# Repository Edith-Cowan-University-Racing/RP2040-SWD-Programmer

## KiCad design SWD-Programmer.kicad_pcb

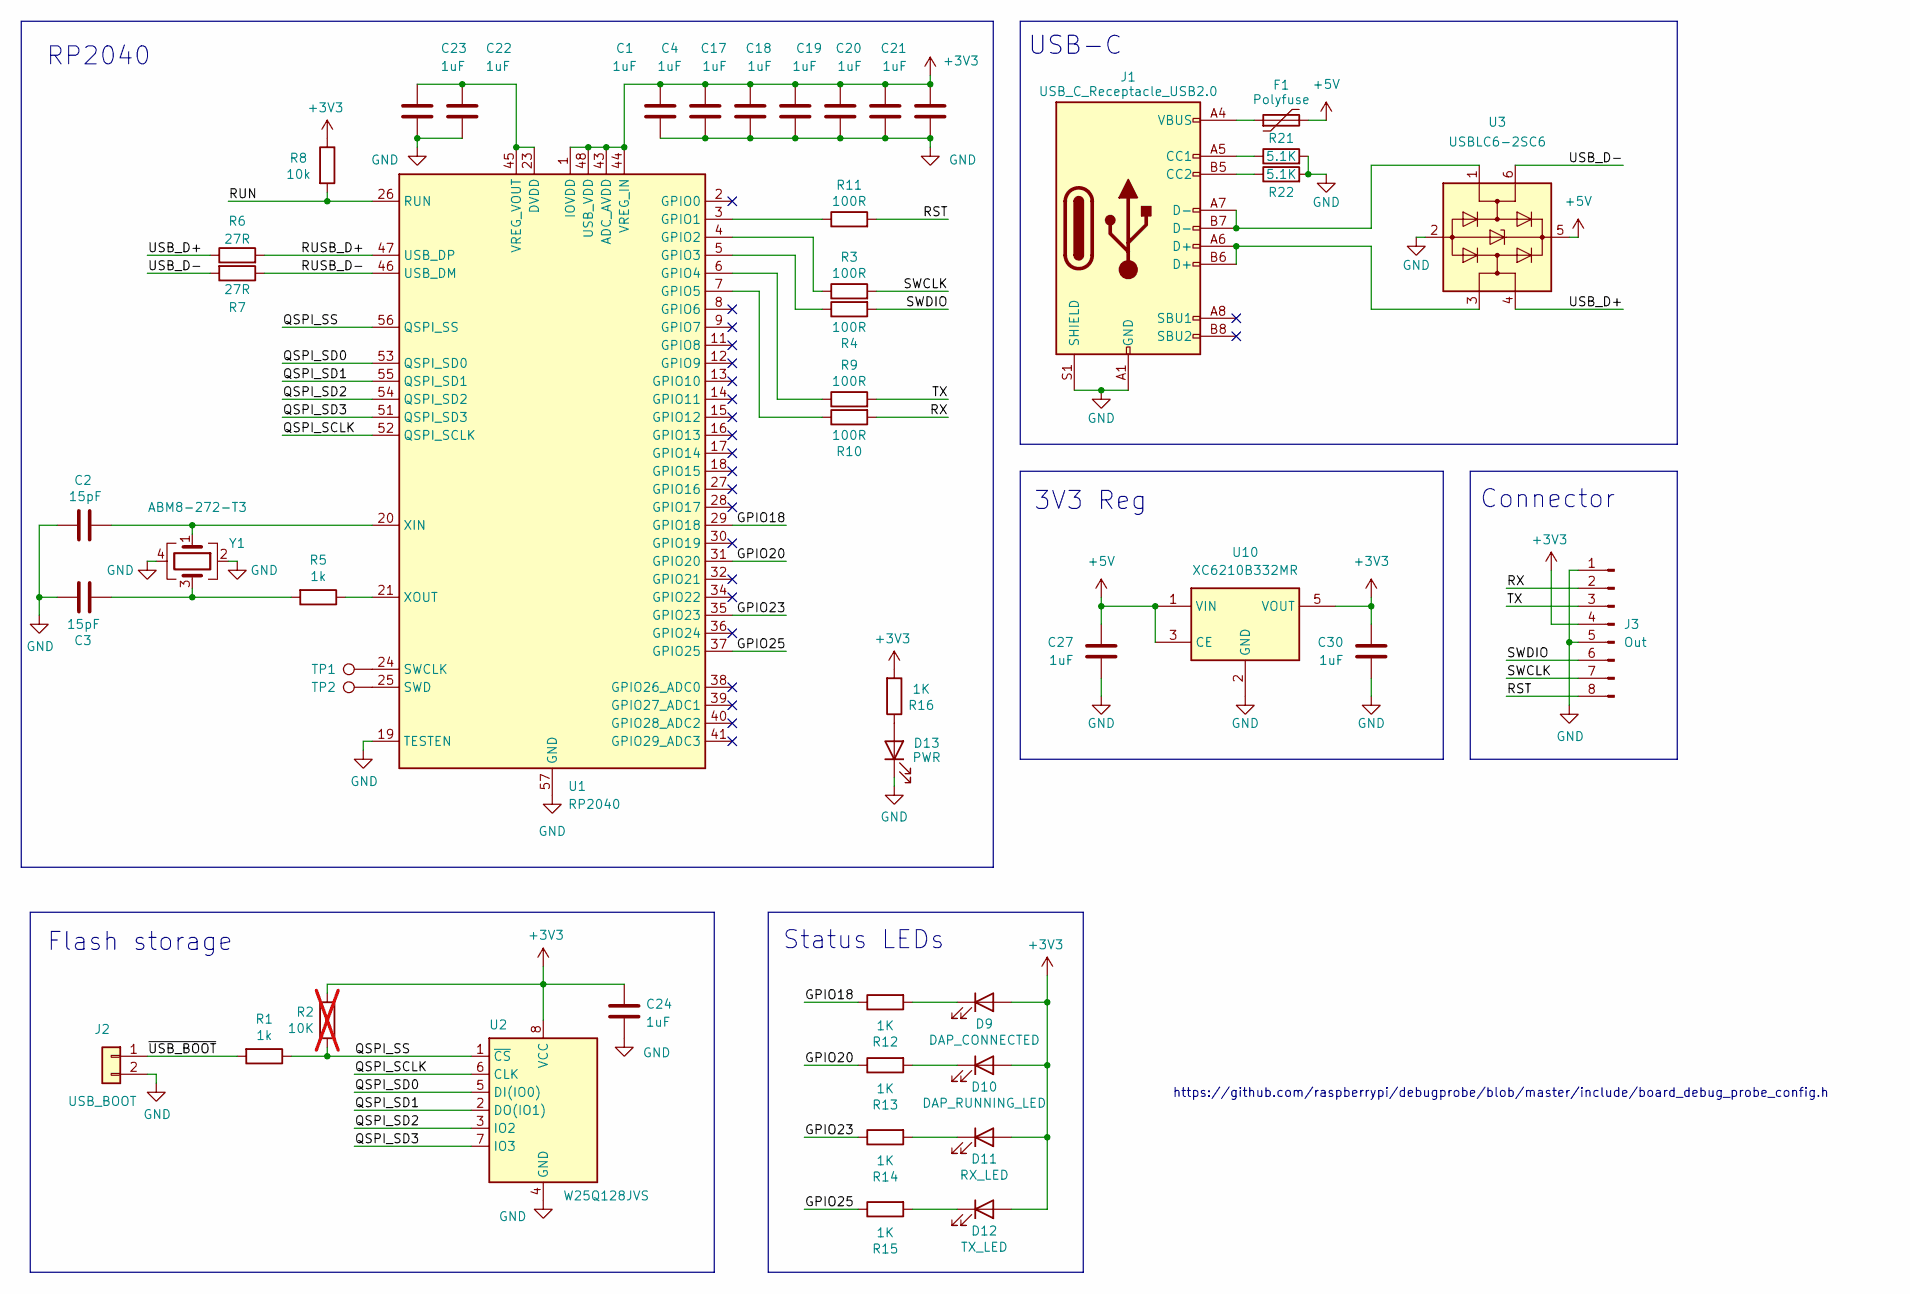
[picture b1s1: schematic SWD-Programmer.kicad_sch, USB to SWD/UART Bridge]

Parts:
C1, C4, C17, C18, C19, C20, C21, C22, C23, C24, C27, C30: 1uF; C_0603_1608Metric
C2, C3: 15pF; C_0603_1608Metric
D9: DAP_CONNECTED; LED_0805_2012Metric
D10: DAP_RUNNING_LED; LED_0805_2012Metric
D11: RX_LED; LED_0805_2012Metric
D12: TX_LED; LED_0805_2012Metric
D13: PWR; LED_0805_2012Metric
F1: Polyfuse; Fuse_0805_2012Metric
J1: USB_C_Receptacle_USB2.0; U263-163N-4OS1735
J2: USB_BOOT; PinHeader_1x02_P1.27mm_Vertical
J3: Out; PinHeader_1x08_P2.54mm_Horizontal
R1, R5: 1k; R_0603_1608Metric
R2: 10K; R_0603_1608Metric; not fitted
R3, R4, R9, R10, R11: 100R; R_0603_1608Metric
R6, R7: 27R; R_0603_1608Metric
R8: 10k; R_0603_1608Metric
R12, R13, R14, R15, R16: 1K; R_0603_1608Metric
R21, R22: 5.1K; R_0603_1608Metric
TP1, TP2: TestPoint; TestPoint_Pad_D2.0mm
U1: RP2040; QFN-56-1EP_7x7mm_P0.4mm_EP3.2x3.2mm
U2: W25Q128JVS; SOIC-8_5.3x5.3mm_P1.27mm
U3: USBLC6-2SC6; SOT-23-6; LCSC C2827654
U10: XC6210B332MR; SOT-23-5
Y1: ABM8-272-T3; Crystal_SMD_3225-4Pin_3.2x2.5mm

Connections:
+3V3: C1.1, C4.1, C17.1, C18.1, C19.1, C20.1, C21.1, C24.1, C30.1, D9.2 (A), D10.2 (A), D11.2 (A), D12.2 (A), J3.4, R2.1, R8.1, R16.2, U1.1 (IOVDD), U1.10 (IOVDD), U1.22 (IOVDD), U1.33 (IOVDD), U1.42 (IOVDD), U1.43 (ADC_AVDD), U1.44 (VREG_IN), U1.48 (USB_VDD), U1.49 (IOVDD), U2.8 (VCC), U10.5 (VOUT)
+5V: C27.1, F1.2, U3.5 (VBUS), U10.1 (VIN), U10.3 (CE)
/GPIO18: R12.1, U1.29 (GPIO18)
/GPIO20: R13.1, U1.31 (GPIO20)
/GPIO23: R14.1, U1.35 (GPIO23)
/GPIO25: R15.1, U1.37 (GPIO25)
/QSPI_SCLK: U1.52 (QSPI_SCLK), U2.6 (CLK)
/QSPI_SD0: U1.53 (QSPI_SD0), U2.5 (DI(IO0))
/QSPI_SD1: U1.55 (QSPI_SD1), U2.2 (DO(IO1))
/QSPI_SD2: U1.54 (QSPI_SD2), U2.3 (IO2)
/QSPI_SD3: U1.51 (QSPI_SD3), U2.7 (IO3)
/QSPI_SS: R1.1, R2.2, U1.56 (QSPI_SS), U2.1 (~CS)
/RST: J3.8, R11.2
/RUN: R8.2, U1.26 (RUN)
/RUSB_D+: R6.2, U1.47 (USB_DP)
/RUSB_D-: R7.1, U1.46 (USB_DM)
/RX: J3.2, R10.2
/SWCLK: J3.7, R3.2
/SWDIO: J3.6, R4.2
/TX: J3.3, R9.2
/USB_D+: R6.1, U3.4 (I/O2)
/USB_D-: R7.2, U3.6 (I/O1)
/~USB_BOOT: J2.1, R1.2
GND: C1.2, C2.2, C3.2, C4.2, C17.2, C18.2, C19.2, C20.2, C21.2, C22.2, C23.2, C24.2, C27.2, C30.2, D13.1 (K), J1.A1 (GND), J1.A12 (GND), J1.B1 (GND), J1.B12 (GND), J1.S1 (SHIELD), J2.2, J3.1, J3.5, R21.2, R22.2, U1.19 (TESTEN), U1.57 (GND), U2.4 (GND), U3.2 (GND), U10.2 (GND), Y1.2, Y1.4
unnamed: C3.1, R5.2, Y1.3
unnamed: D9.1 (K), R12.2
unnamed: D10.1 (K), R13.2
unnamed: D11.1 (K), R14.2
unnamed: D12.1 (K), R15.2
unnamed: D13.2 (A), R16.1
unnamed: F1.1, J1.A4 (VBUS), J1.A9 (VBUS), J1.B4 (VBUS), J1.B9 (VBUS)
unnamed: J1.A5 (CC1), R21.1
unnamed: J1.B5 (CC2), R22.1
unnamed: J1.A6 (D+), J1.B6 (D+), U3.3 (I/O2)
unnamed: J1.A7 (D-), J1.B7 (D-), U3.1 (I/O1)
unnamed: R11.1, U1.3 (GPIO1)
unnamed: R3.1, U1.4 (GPIO2)
unnamed: R4.1, U1.5 (GPIO3)
unnamed: R9.1, U1.6 (GPIO4)
unnamed: R10.1, U1.7 (GPIO5)
unnamed: TP1.1, U1.24 (SWCLK)
unnamed: TP2.1, U1.25 (SWD)
unnamed: C22.1, C23.1, U1.23 (DVDD), U1.45 (VREG_VOUT), U1.50 (DVDD)
unnamed: C2.1, U1.20 (XIN), Y1.1
unnamed: R5.1, U1.21 (XOUT)

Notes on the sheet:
https://github.com/raspberrypi/debugprobe/blob/master/include/board_debug_probe_config.h
RP2040
USB-C
Connector
Flash storage
3V3 Reg
Status LEDs

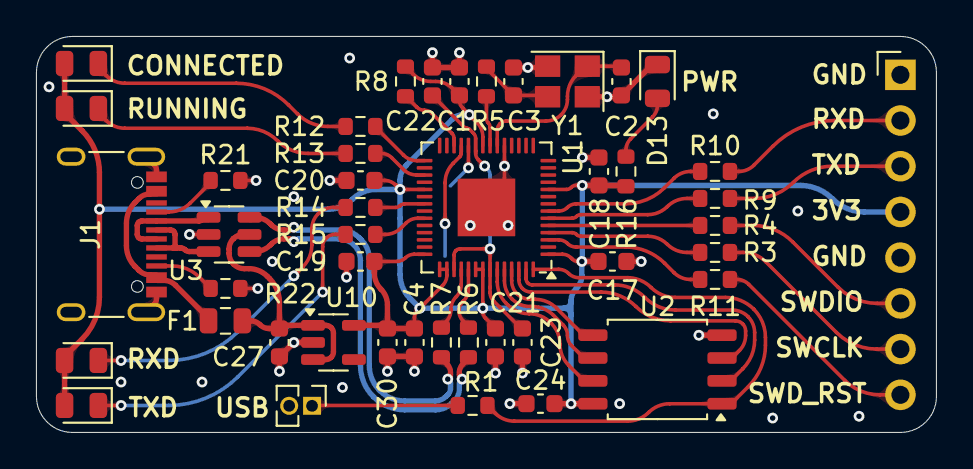
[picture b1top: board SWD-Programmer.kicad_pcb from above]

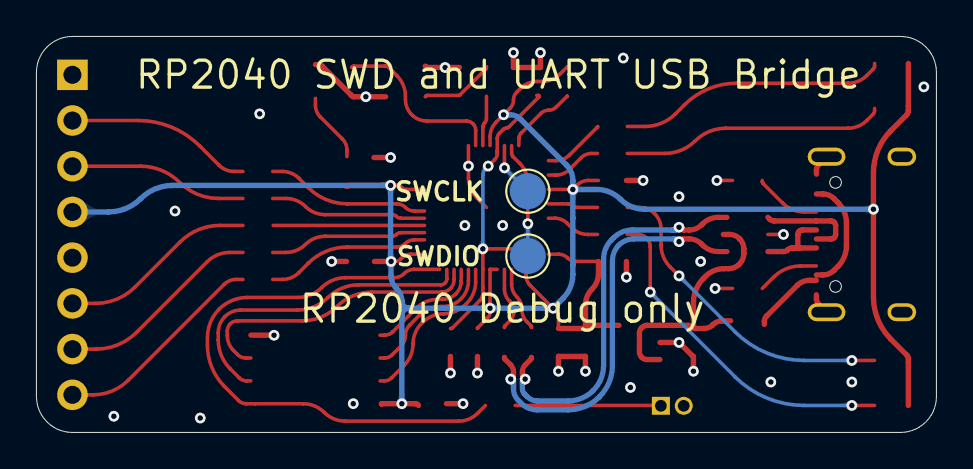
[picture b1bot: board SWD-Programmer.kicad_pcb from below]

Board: 4 copper layers, 50.0 x 22.0 mm, 47 parts (2 on the bottom side), 45 nets.

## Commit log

2025-07-04 Board files
2025-07-05 Pcb cleanup
2025-07-07 Curved traces and teardrops
